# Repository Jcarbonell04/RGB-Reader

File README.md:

# RGB Reader

**Abstract**

I will be attempting to create a small colour reader device. The RGB Reader will include a colour sensor to read the rgb values and oled sceen to display. For the demo, I intend to to get paint sample strips of red, green, and, blue when I demo my reader.

**Hardware**

I have chosen the [STM32G031](https://www.digikey.ca/en/products/detail/stmicroelectronics/STM32G031K6T6/10300266?gclsrc=aw.ds&gad_source=1&gad_campaignid=17336435733&gbraid=0AAAAADrbLlg0N1Kd5EXrgzAC7LUfLDUnC&gclid=CjwKCAjwiY_GBhBEEiwAFaghvhG4pRAglKmtf1LMJkXjHH9BUgq6LzggdycpZ285lm5ClKIdZo-x5xoCx5gQAvD_BwE) as the microcontroller as there are resources given from the instructor to give me a soft start. I have not this microcontroller before, so I will have to do some research.
Supply Voltage: 1.7 V to 3.6 V

The RGB Reader will be based on a photoelectric/colour sensor. From a wide selection, I have chosen the [TCS34725 COLOR LIGHT-TO-DIGITAL CONVERTER](https://cdn-shop.adafruit.com/datasheets/TCS34725.pdf). I intend to use it because it contains an I<sup>2</sup>C interface, but seeing it is a popular choice with the STM32 gives me more confidence in choosing it. I do not have a library at the moment, but adafruit has library support for the arduino so I can start from there.
Supply Voltage: 2.7 V to 3.6 V

The display to the user will be a standard [SSD1306 128x64 I2C OLED display](https://www.amazon.ca/IZOKEE-Display-SSD1306-Raspberry-Yellow-Blue-IIC/dp/B076PNP2VD/ref=sr_1_4?crid=YXRJPVLMW9EL&dib=eyJ2IjoiMSJ9.OiybhU4XaNG6ShwJSbKTDJvkYVE5uWbfoGIpsV5YLpBxJZDEaTAqdDtPy0tWRoJ52zOXuq_cxh_j7TJz6rQsvuurKs-8koC1GKyBl8pSYDMVw_H9vG4T5x3UwTL4c-0G3metweLWxYmtzTT2dfp_ICcF3H6XFZ6SrumeL0oEe4TA_5mWreyuYLR2lQpLqmIKqqdcu85n4UoGaor2EPOOpFk7buL7VHgKdXirYBa8lvgnERpXD73-6vSLab_szAls09LM63wOs_da7XiV6JCm6I8Yke89vqq1vI80AT_NoQA.8lL2_YlI-GB7R8w4wl2GavAd1IDedNfI48C0q6DILyc&dib_tag=se&keywords=ssd1306&qid=1757697723&s=electronics&sprefix=ssd1306%2Celectronics%2C93&sr=1-4). I will be leveraging the libraries resourced from the class BrightSpace.

Supply Voltage: The logic and I2C interface for the SSD1306 typically operate at 3.3V or 5V. 
Panel Voltage: The OLED panel itself requires a higher voltage, usually between 7V and 15V, to light  the pixels. (STILL IT ONLY NEEDS 5V)
Onboard Circuitry: Many SSD1306 boards include an integrated charge pump or boost regulator, which takes the input voltage and generates the higher voltage needed by the panel. 

This device doesn't really need to be portable, so I can power it using a micro usb.

**Research**

Things I don't know, that I will need to do research on:
- Using [SEGGER](https://www.segger.com/downloads/embedded-studio/), I haven't done it before. I will need to refer to some tutorials to get started.
- I have briefly looked at the TCS34725, all I saw was that it was poplular, uses I<sup>2</sup>C too. There are many resources on the internet for this specific sensor which gives me more confidence
- I will need to research how to implement a micro usb plug in for my design. I will need it to program and power my microcontroller
  
**Proof of Concept**

For my proof-of-life build, I will be using a development board that fits into a breadboard. I have chosen the presxisting [NUCLEO-G031K8](https://www.digikey.ca/en/products/detail/stmicroelectronics/NUCLEO-G031K8/10321671?s=N4IgTCBcDaIHIFcDGAbApgewAQHEAMAzAIwgC6AvkA) for my build. This will be powered with a USB connector from a host pc. I probably have a cable for this at home

**Stretch Goals**

If I enough time is permitted, I would like to try adding a RBG light to replicate the colour values from the sensor. The only issues that I have is relying on true colour detection. Amibient light could affect the true colour. I can decide this later.

**Final Build**

For my Final build, I would like to design and 3D Print a case for my RGB Reader. My main concern is that I do not have too much experience 3D printing, so I will have to do some research. For designing, I will the software [TinkerCAD](https://www.tinkercad.com/). I have used TinkerCAD before, but never got the chance or oppurtunity to physically print out anything. I need to design my case to enclose the sensor in a way where amibient light does not affect the values read. For example, the cool lighting could affect the output by increasing the B value.

The PCB will include the main components listed earlier. The only difference between the PCB build and the proof of life build the use of the Nucleo development board in the breadboard version. I will have to design my PCB and case to allocate space for the programmer, and other parts needed for it to work. More research needs to be done before I get to the case desgining.

**Unpopulated PCB Photos**

**Schedule**

Week 1-2:
- [x] Finalize Design (Project Proposal)
- [x] Procure proof-of-life components (MCU carrier, battery options)

Week 3-4:
- [x] Assemble proof-of-life components
- [x] Master toolchain, begin software development

Week 5-6:
- [x] Finalize design, complete initial software design

Week 7-9:
- [x] Complete PCB design, software essentially complete
- [x] Complete dimensions for case know, begin 3D case design around PCB dimensions

Week 10:
- [x] Send out PCB design for manufacture

When PCBs arrive:
- [x] assemble, program, and test with current software.
- [x] complete added features, assemble into case

Finished Dec 12 2025!

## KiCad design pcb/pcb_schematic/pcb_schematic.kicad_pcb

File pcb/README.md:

# PCB Design

All design files for your PCB version of your project go here.

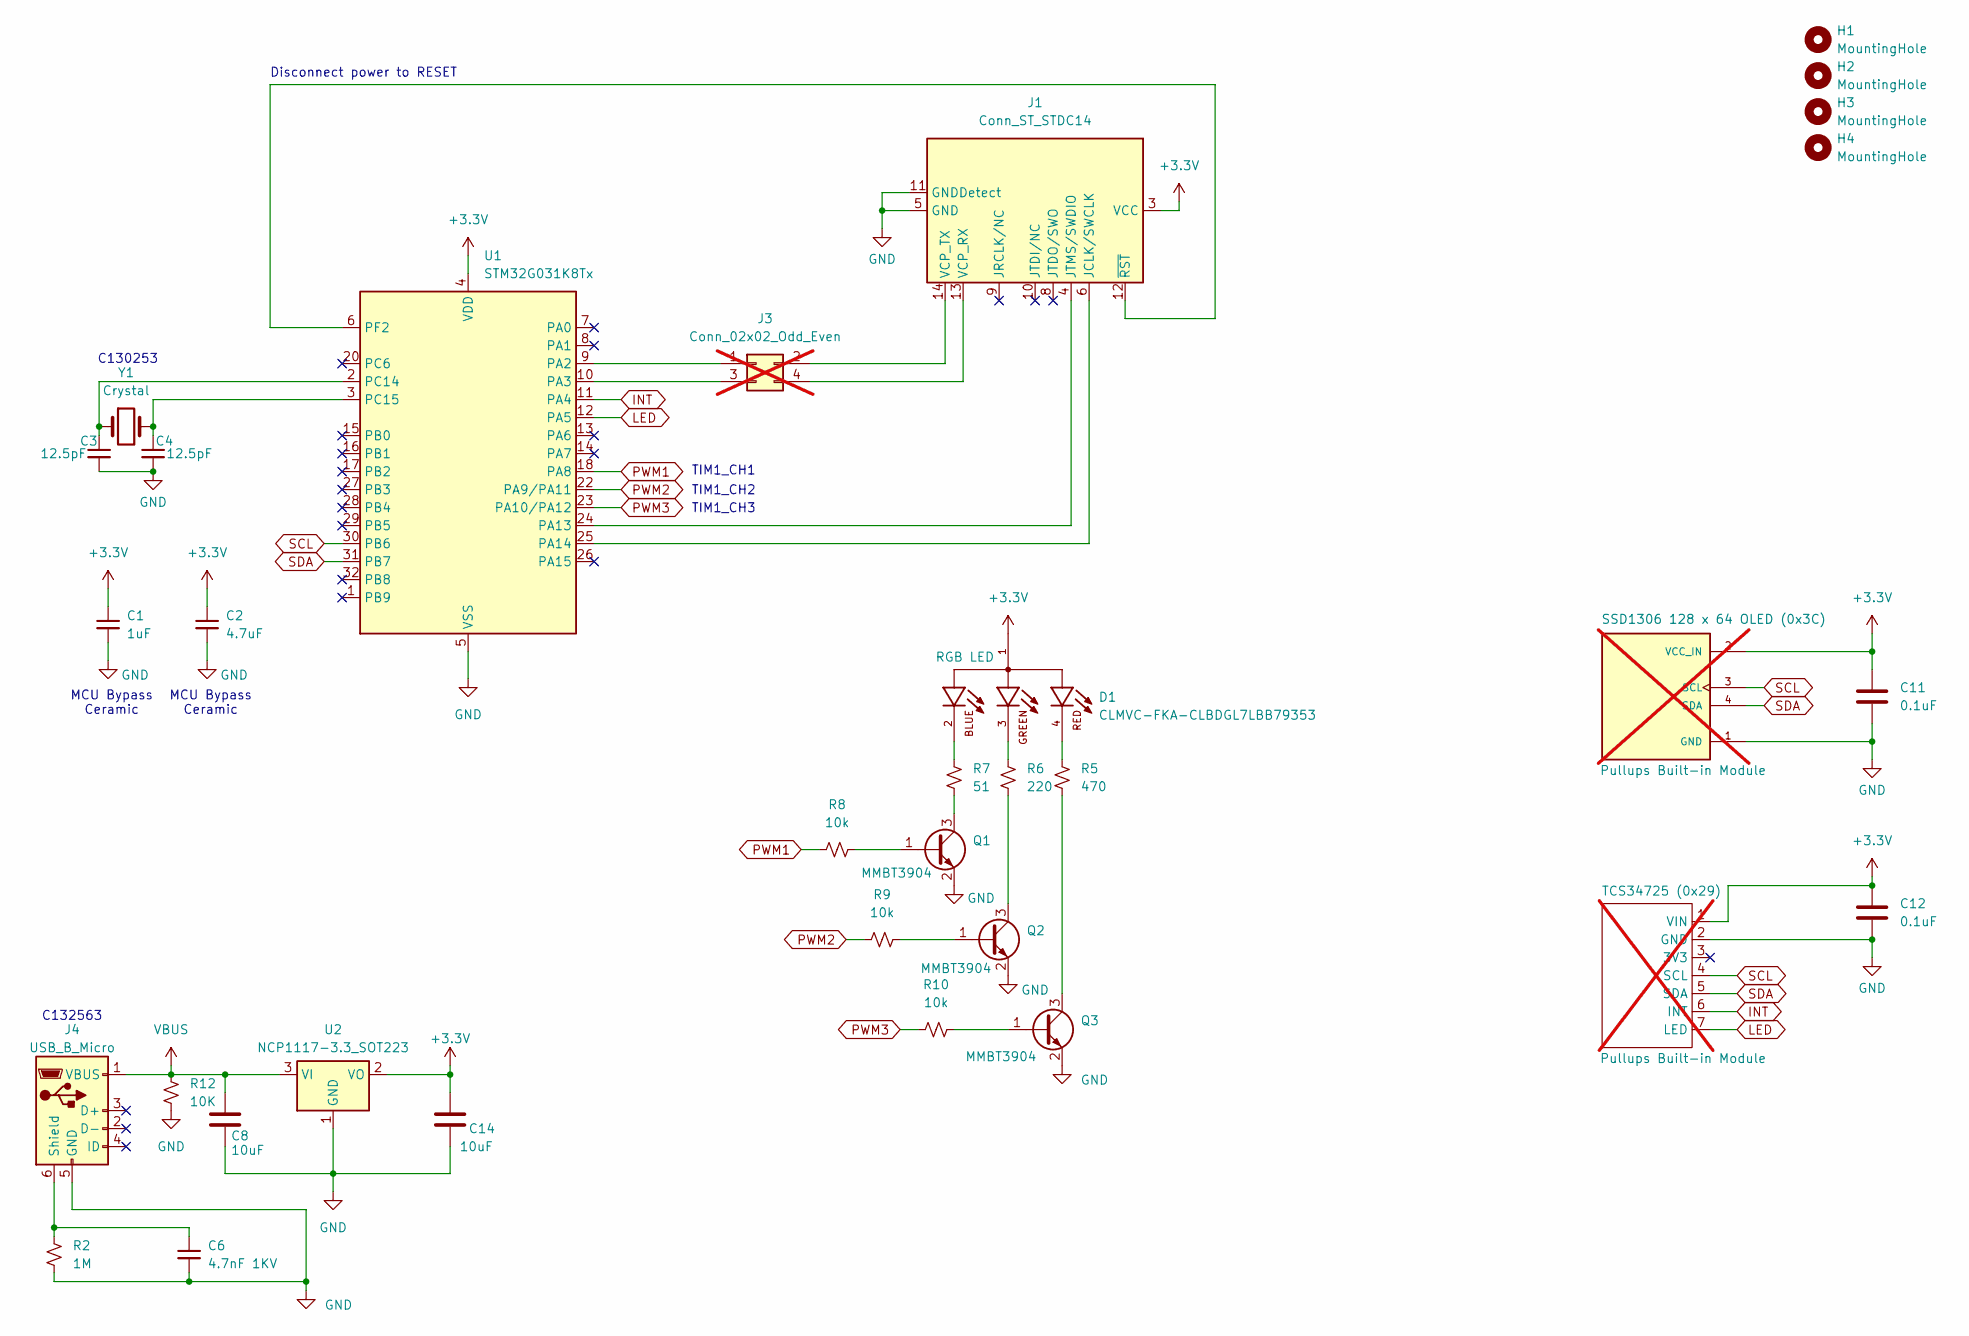
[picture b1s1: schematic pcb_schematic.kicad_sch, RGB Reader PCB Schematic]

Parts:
C1: 1uF; C_0805_2012Metric
C2: 4.7uF; C_0805_2012Metric
C3, C4: 12.5pF; C_0805_2012Metric
C6: 4.7nF 1KV; C_0805_2012Metric
C8, C14: 10uF; C_0805_2012Metric
C11, C12: 0.1uF; C_0805_2012Metric
D1: CLMVC-FKA-CLBDGL7LBB79353; LED_CLMVC-FKA-CLBDGL7LBB79353; PARTREV 14
H1, H2, H3, H4: MountingHole; MountingHole_3.2mm_M3
J1: Conn_ST_STDC14; PinHeader_2x07_P1.27mm_Vertical_SMD
J3: Conn_02x02_Odd_Even; PinHeader_2x02_P2.54mm_Vertical; not fitted
J4: USB_B_Micro; USB_Micro-B_Amphenol_10118194_Horizontal
Q1, Q2, Q3: MMBT3904; SOT-23
R2: 1M; R_0805_2012Metric
R5: 470; R_0805_2012Metric
R6: 220; R_0805_2012Metric
R7: 51; R_0805_2012Metric
R8, R9, R10: 10k; R_0805_2012Metric
R12: 10K; R_0805_2012Metric
U1: STM32G031K8Tx; LQFP-32_7x7mm_P0.8mm
U2: NCP1117-3.3_SOT223; SOT-223-3_TabPin2
U4: SSD1306 128 x 64 OLED (0x3C); 128x64OLED; PARTREV 2018-09-10; not fitted
U5: TCS34725 (0x29); TCS34725; not fitted
Y1: Crystal; Crystal_SMD_3215-2Pin_3.2x1.5mm

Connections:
+3.3V: C1.1, C2.1, C11.1, C12.1, C14.2, D1.1, J1.3 (VCC), U1.4 (VDD), U2.2 (VO), U4.2 (VCC_IN), U5.1 (VIN)
GND: C1.2, C2.2, C3.2, C4.2, C6.2, C8.1, C11.2, C12.2, C14.1, J1.5 (GND), J1.7 (GND), J1.11 (GNDDetect), J4.5 (GND), Q1.2 (E), Q2.2 (E), Q3.2 (E), R2.2, R12.1, U1.5 (VSS), U2.1 (GND), U4.1 (GND), U5.2 (GND)
INT: U1.11 (PA4), U5.6 (INT)
LED: U1.12 (PA5), U5.7 (LED)
unnamed: D1.2, R7.1
unnamed: D1.3, R6.1
unnamed: D1.4, R5.1
unnamed: J1.6 (JCLK/SWCLK), U1.25 (PA14)
unnamed: J1.4 (JTMS/SWDIO), U1.24 (PA13)
unnamed: J1.13 (VCP_RX), J3.4
unnamed: J1.14 (VCP_TX), J3.2
unnamed: J1.12 (~RST), U1.6 (PF2)
unnamed: J3.1, U1.9 (PA2)
unnamed: J3.3, U1.10 (PA3)
unnamed: C6.1, J4.6 (Shield), R2.1
unnamed: Q1.1 (B), R8.2
unnamed: Q1.3 (C), R7.2
unnamed: Q2.1 (B), R9.2
unnamed: Q2.3 (C), R6.2
unnamed: Q3.1 (B), R10.2
unnamed: Q3.3 (C), R5.2
unnamed: C3.1, U1.2 (PC14), Y1.1
unnamed: C4.1, U1.3 (PC15), Y1.2
PWM1: R8.1, U1.18 (PA8)
PWM2: R9.1, U1.22 (PA9/PA11)
PWM3: R10.1, U1.23 (PA10/PA12)
SCL: U1.30 (PB6), U4.3 (SCL), U5.4 (SCL)
SDA: U1.31 (PB7), U4.4 (SDA), U5.5 (SDA)
VBUS: C8.2, J4.1 (VBUS), R12.2, U2.3 (VI)

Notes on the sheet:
TIM1_CH3
TIM1_CH2
TIM1_CH1
C132563
MCU Bypass Ceramic
Disconnect power to RESET
C130253

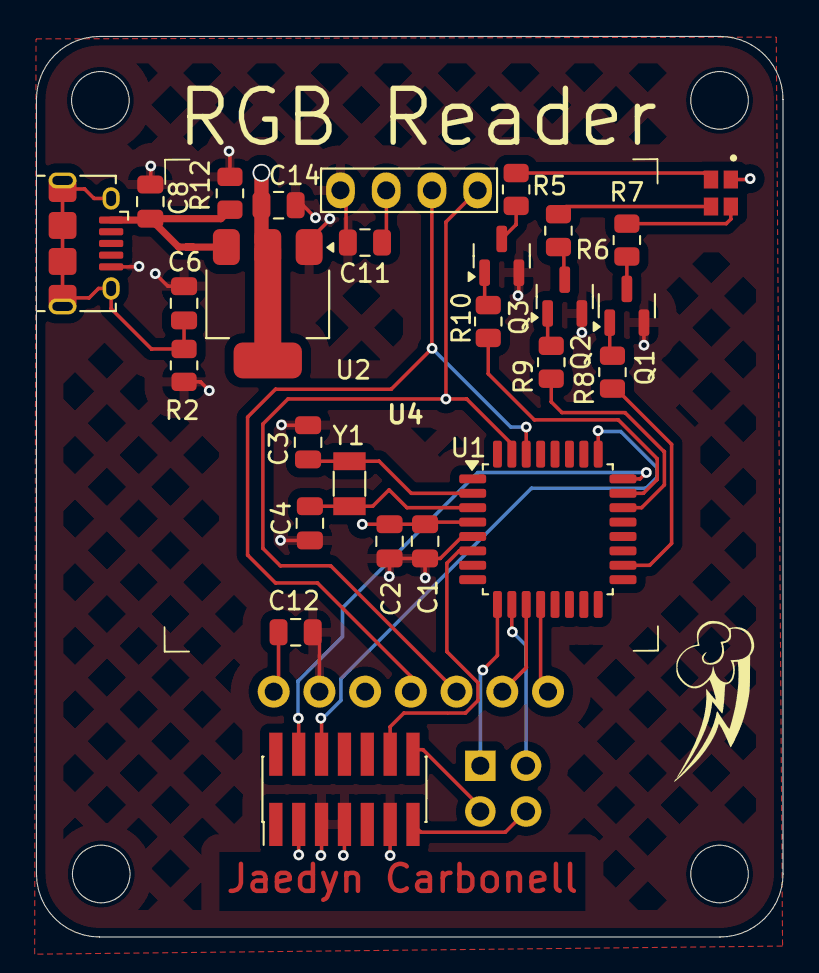
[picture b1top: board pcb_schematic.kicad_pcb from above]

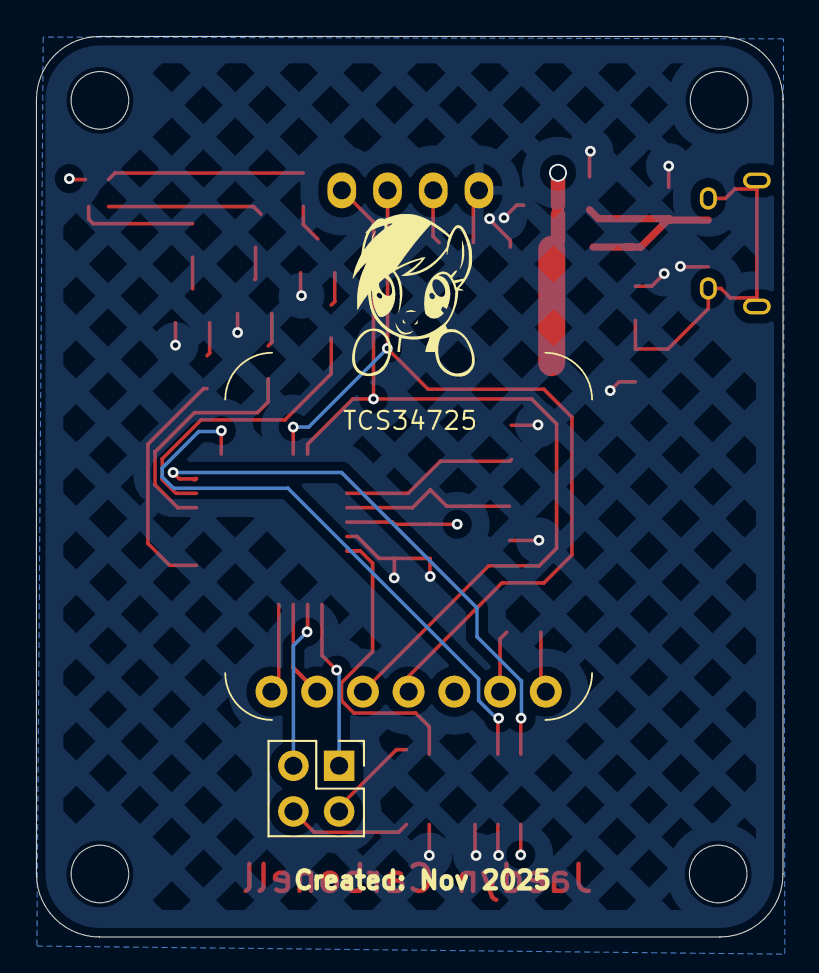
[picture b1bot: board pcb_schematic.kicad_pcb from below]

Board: 4 copper layers, 41.5 x 50.0 mm, 33 parts (2 on the bottom side), 29 nets.

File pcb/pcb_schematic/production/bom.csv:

Designator,Footprint,Quantity,Value,LCSC Part #
C1,0805,1,1uF,
"C11, C12",0805,2,0.1uF,
"C14, C8",0805,2,10uF,
C2,0805,1,4.7uF,
"C3, C4",0805,2,12.5pF,
C6,0805,1,4.7nF 1KV,
D1,LED_CLMVC-FKA-CLBDGL7LBB79353,1,CLMVC-FKA-CLBDGL7LBB79353,
J1,PinHeader_2x07_P1.27mm_Vertical_SMD,1,Conn_ST_STDC14,
J4,USB_Micro-B_Amphenol_10118194_Horizontal,1,USB_B_Micro,
"Q1, Q2, Q3",SOT-23,3,MMBT3904,
"R10, R12, R8, R9",0805,4,10k,
R2,0805,1,1M,
R5,0805,1,470,
R6,0805,1,220,
R7,0805,1,51,
U1,LQFP-32_7x7mm_P0.8mm,1,STM32G031K8Tx,
U2,SOT-223-3_TabPin2,1,NCP1117-3.3_SOT223,
Y1,Crystal_SMD_3215-2Pin_3.2x1.5mm,1,Crystal,

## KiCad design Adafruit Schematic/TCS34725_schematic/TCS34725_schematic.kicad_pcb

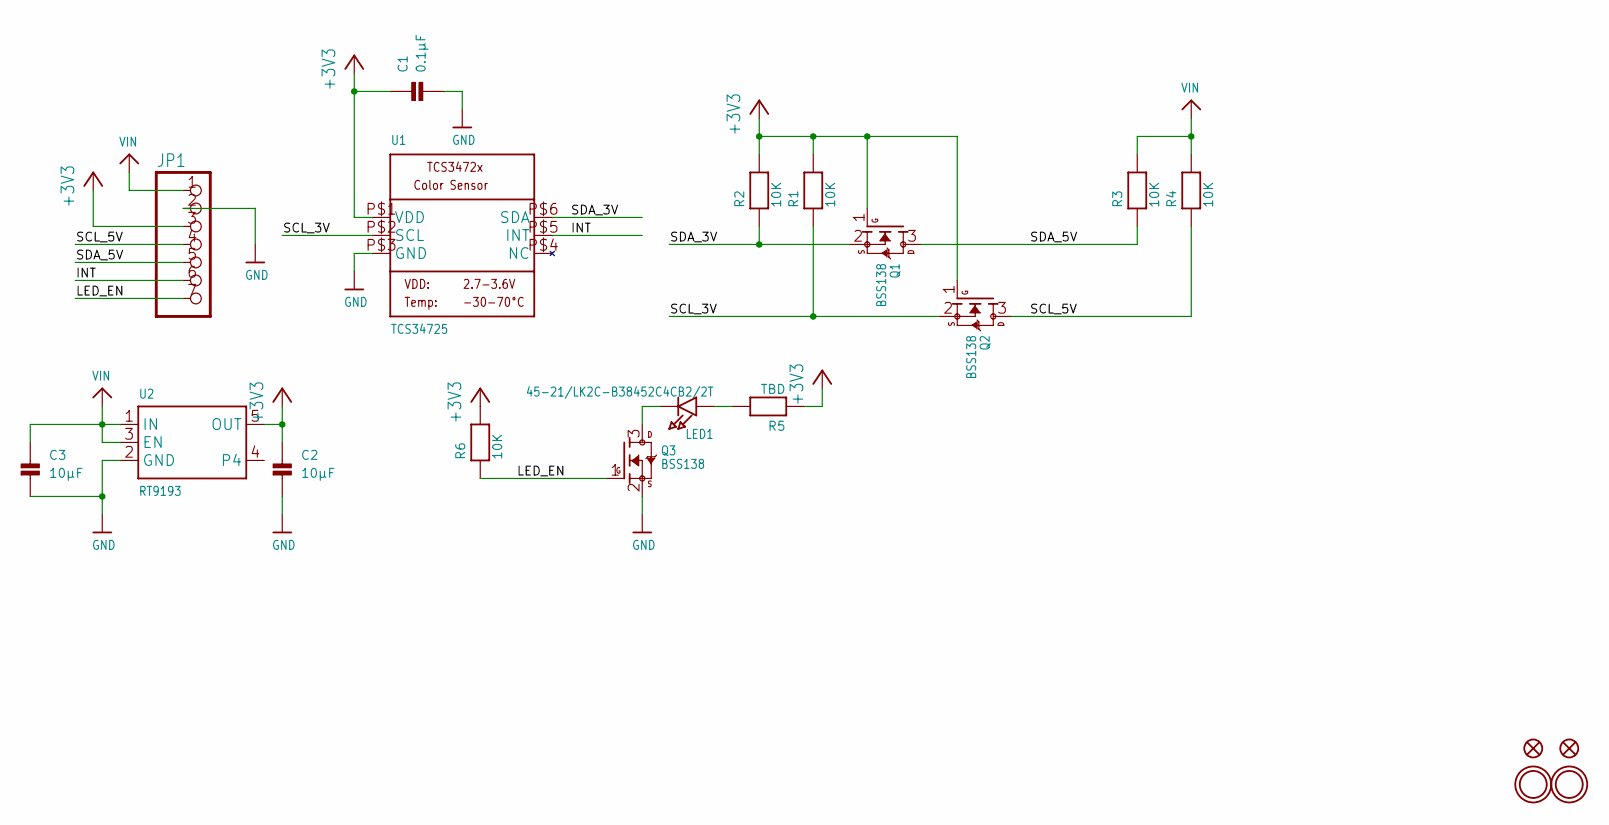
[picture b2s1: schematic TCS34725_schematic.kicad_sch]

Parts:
C1: 0.1µF; _0805
C2, C3: 10µF; _0805
FID1, FID2: FIDUCIAL""; FIDUCIAL_1MM
JP1: HEADER-1X770MIL; 1X07_ROUND_70
LED1: 45-21/LK2C-B38452C4CB2/2T; EVERLIGHT_45-21
Q1, Q2, Q3: BSS138; SOT23-WIDE
R1, R2, R3, R4, R6: 10K; _0805
R5: TBD; _0805
U1: TCS34725; TCS3472_FN6
U2: RT9193; SOT23-5
U$8, U$14: MOUNTINGHOLE2.5; MOUNTINGHOLE_2.5_PLATED

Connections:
+3V3: C1.1, C2.1, JP1.3, Q1.1 (G), Q2.1 (G), R1.2, R2.2, R5.1, R6.2, U1.P$1 (VDD), U2.5 (OUT)
GND: C1.2, C2.2, C3.2, JP1.2, Q3.2 (S), U1.P$3 (GND), U2.2 (GND)
INT: JP1.6, U1.P$5 (INT)
LED_EN: JP1.7, Q3.1 (G), R6.1
unnamed: LED1.K (C), Q3.3 (D)
unnamed: LED1.A, R5.2
SCL_3V: Q2.2 (S), R1.1, U1.P$2 (SCL)
SCL_5V: JP1.4, Q2.3 (D), R4.1
SDA_3V: Q1.2 (S), R2.1, U1.P$6 (SDA)
SDA_5V: JP1.5, Q1.3 (D), R3.1
VIN: C3.1, JP1.1, R3.2, R4.2, U2.1 (IN), U2.3 (EN)

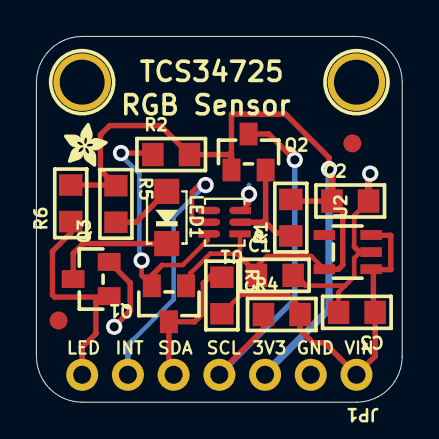
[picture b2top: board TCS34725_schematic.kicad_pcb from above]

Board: 2 copper layers, 20.3 x 20.3 mm, 22 parts (1 on the bottom side), 11 nets.

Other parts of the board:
U$2: ADAFRUIT_2.5MM
U$18: ADAFRUIT_5MM

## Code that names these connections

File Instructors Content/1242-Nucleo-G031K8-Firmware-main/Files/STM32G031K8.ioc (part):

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Mcu.Name=STM32G031K(4-6-8)Tx
Mcu.Package=LQFP32
Mcu.UserName=STM32G031K8Tx
PA10.Mode=I2C
PA10.Signal=I2C1_SDA
PA13.GPIOParameters=GPIO_Label
PA13.GPIO_Label=T_JTMS
PA13.Mode=Serial_Wire
PA13.Signal=SYS_SWDIO
PA14-BOOT0.GPIOParameters=GPIO_Label
PA14-BOOT0.GPIO_Label=T_JTCK
PA14-BOOT0.Mode=Serial_Wire
PA14-BOOT0.Signal=SYS_SWCLK
PA2.GPIOParameters=GPIO_PuPd,GPIO_Label
PA2.GPIO_Label=T_VCP_TX
PA2.GPIO_PuPd=GPIO_PULLUP
PA2.Mode=Asynchronous
PA2.Signal=USART2_TX
PA3.GPIOParameters=GPIO_PuPd,GPIO_Label
PA3.GPIO_Label=T_VCP_RX
PA3.GPIO_PuPd=GPIO_PULLUP
PA3.Mode=Asynchronous
PA3.Signal=USART2_RX
PA8.Mode=Clock-out
PA8.Signal=RCC_MCO
PA9.Mode=I2C
PA9.Signal=I2C1_SCL
PC14-OSC32_IN\ (PC14).Mode=LSE-External-Oscillator
PC14-OSC32_IN\ (PC14).Signal=RCC_OSC32_IN
PC15-OSC32_OUT\ (PC15).Mode=LSE-External-Oscillator
PC15-OSC32_OUT\ (PC15).Signal=RCC_OSC32_OUT
PC6.GPIOParameters=GPIO_Label
PC6.GPIO_Label=LD3 [Green]
PC6.Signal=GPIO_Output
PF2\ -\ NRST.GPIOParameters=GPIO_Label
PF2\ -\ NRST.GPIO_Label=T_NRST
PF2\ -\ NRST.Signal=GPXTI2
RCC.HSE_VALUE=8000000
RCC.SYSCLKFreq_VALUE=25000000
RCC.SYSCLKSource=RCC_SYSCLKSOURCE_PLLCLK
board=NUCLEO-G031K8
boardIOC=true

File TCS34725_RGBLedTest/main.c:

// Author: Jaedyn Carbonell
// Desc: Reading RGB values on SSD1306 (OLED) from TCS34725 (colour sensor) + LED
// Core clock: 64MHz
// Notes:
// Requires I2C1 on PB6/PB7 (SCL/SDA) to communicate with OLED
// PA8  - TIM1 CH1 R
// PA9  - TIM1 CH2 G
// PA10 - TIM1 CH3 B


#include "stm32g031xx.h"
#include <stdio.h>
#include "gpio.h"
#include "pll.h"
#include "usart.h"
#include "i2c.h"
#include "SSD1306.h"
#include "TCS34725.h"

// function prototypes
void _OneTimeInits(void);
uint16_t ScaleToPWM(uint16_t val, uint16_t clear);

TCS34725_t colourSensor;

const uint16_t PWM_MAX = 63999;

uint16_t ScaleToPWM(uint16_t val, uint16_t clear)
{
    if (clear == 0) return 0;

    float norm = (float)val / (float)clear; 
    float pwm  = norm * PWM_MAX;

    if (pwm < 0)       pwm = 0;
    if (pwm > PWM_MAX) pwm = PWM_MAX;

    return (uint16_t)pwm;
}

// -----------------------------------------------------
int main(void)
{
    _PLL_To_64();
    _OneTimeInits();

    _USART2_TxStringXY(1, 6, "Initializing TCS34725...");

    // Initialize sensor
    if (!_TCS34725_Init(&colourSensor))
    {
        _USART2_TxStringXY(1, 7, "TCS34725 not found!");
        _SSD1306_StringXY(0, 0, "TCS34725 not found!");
        _SSD1306_Render();
        while (1);
    }

    _USART2_TxStringXY(1, 7, "TCS34725 ready!");
    _SSD1306_Clear();
    _SSD1306_StringXY(0, 0, "TCS34725 ready!");
    _SSD1306_Render();

    uint16_t r, g, b, c;
    char buff[64];

    while (1)
    {
        // Read raw sensor data
        _TCS34725_GetRawData(&colourSensor, &r, &g, &b, &c);

        // PWM UPDATE FOR RGB LED 
        TIM1->CCR1 = ScaleToPWM(r, c);   // Red
        TIM1->CCR2 = ScaleToPWM(g, c);   // Green
        TIM1->CCR3 = ScaleToPWM(b, c);   // Blue

        // OLED Display
        _SSD1306_Clear();
        sprintf(buff, "R:%5u", r);
        _SSD1306_StringXY(0, 0, buff);
        sprintf(buff, "G:%5u", g);
        _SSD1306_StringXY(0, 1, buff);
        sprintf(buff, "B:%5u", b);
        _SSD1306_StringXY(0, 2, buff);
        sprintf(buff, "C:%5u", c);
        _SSD1306_StringXY(0, 3, buff);
        _SSD1306_Render();

        // Serial Output
        sprintf(buff, "R:%u G:%u B:%u C:%u\r\n", r, g, b, c);
        _USART2_TxString(buff);

        for (volatile int i = 0; i < 500000; ++i); // ~500ms delay
    }
}

// -----------------------------------------------------
void _OneTimeInits(void)
{
    RCC->APBENR2 |= RCC_APBENR2_SYSCFGEN;
    SYSCFG->CFGR1 |= SYSCFG_CFGR1_PA11_RMP;
    SYSCFG->CFGR1 |= SYSCFG_CFGR1_PA12_RMP;

    // GPIOA Clock
    RCC->IOPENR |= RCC_IOPENR_GPIOAEN;

    // USART
    _USART2_Init(64E6, 38400);
    _USART2_ClearScreen();
    _USART2_TxStringXY(1, 1, "USART started...");

    // I2C1
    _USART2_TxStringXY(1, 3, "Starting I2C1 bus...");
    _I2C1_Init_PB67(100);
    _USART2_TxStringXY(1, 4, "I2C1 bus ready...");

    // OLED
    _SSD1306_DispInit(_SSD1306_OR_DOWN);
    _SSD1306_DisplayOn();
    _SSD1306_Clear();
    _SSD1306_StringXY(0, 0, "OLED Ready");
    _SSD1306_Render();

    //                 RGB LED PWM (TIM1 CH1/CH2/CH3)

    RCC->APBENR2 |= RCC_APBENR2_TIM1EN; // Enable TIM1

    // PA8 (CH1), PA9 (CH2), PA10 (CH3)
    GPIOA->MODER &= ~(GPIO_MODER_MODE8_Msk | GPIO_MODER_MODE9_Msk | GPIO_MODER_MODE10_Msk);
    GPIOA->MODER |=  (0x2 << GPIO_MODER_MODE8_Pos) |
                     (0x2 << GPIO_MODER_MODE9_Pos) |
                     (0x2 << GPIO_MODER_MODE10_Pos);

    GPIOA->AFR[1] &= ~(0xF << 0 | 0xF << 4 | 0xF << 8);
    GPIOA->AFR[1] |=  (1 << 0) | (1 << 4) | (1 << 8);  // AF1 TIM1

    // PWM Mode 1 for CH1, CH2, CH3
    TIM1->CCMR1 = (6 << 4) | TIM_CCMR1_OC1PE           // CH1
                | (6 << 12) | TIM_CCMR1_OC2PE;         // CH2

    TIM1->CCMR2 = (6 << 4) | TIM_CCMR2_OC3PE;          // CH3

    TIM1->ARR  = PWM_MAX;
    TIM1->CCR1 = 0;
    TIM1->CCR2 = 0;
    TIM1->CCR3 = 0;

    // Enable outputs
    TIM1->CCER |= TIM_CCER_CC1E | TIM_CCER_CC2E | TIM_CCER_CC3E;

    // Main output enable, TIM1 is advanced timer
    TIM1->BDTR |= TIM_BDTR_MOE;

    TIM1->CR1 |= TIM_CR1_ARPE | TIM_CR1_CEN;
}

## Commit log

2025-09-24 Added simons lib
2025-09-24 Added Instructors Content
2025-09-26 Oled working
2025-09-26 Proof of Life?
2025-10-02 changed
2025-10-03 organize
2025-10-03 bruh
2025-10-07 working?
2025-10-08 soldered lol
2025-10-10 recieved POL checkoff
2025-10-10 added to lib
2025-10-10 lib?
2025-10-13 omg sensor working?
2025-10-13 working!
2025-10-15 help
2025-10-17 xganges
2025-10-22 finished breadboard schematic
2025-10-22 reorganized
2025-10-22 i lowkey dont know what im doing
2025-10-22 oct 22
2025-10-29 bluh
2025-10-29 v4 now?
2025-10-31 Create fp-lib-table
2025-10-31 puth
2025-10-31 almost checkoff
2025-11-04 Changed after recieving feedback
2025-11-04 PWM on Timer 1 Pins
2025-11-05 the schmatic keeps chaning i wanna cry
2025-11-05 Components are laid out
2025-11-06 before i change many thing
2025-11-06 moved rbg led
2025-11-06 Created pcb desgin, need to rid of all warning
2025-11-07 fixerd some warnings with the silkscreen
2025-11-07 Fixed according to feedback
    Schematic -> looks like the current limiting resistors for the read and blue LEDs are reversed.
    Bypass caps for the MCU are drawn really weird!
    Looks like you moved the XTAL and now you have two redundant wires.
    PCB -> Identification is in the copper layer, not the silk layer.
    C12 does not need vias, the through-hole header serves as vias.
    You've got a split on the SDA line of the MCU - try to route from a via, or another pad if you can.
2025-11-08 via error
2025-11-08 via warning
2025-11-08 added image lol
2025-11-08 Finalized?
2025-11-09 ready to order :D
2025-11-20 new project
2025-11-21 change display
2025-12-05 Revise project proposal title and abstract
    Updated the project proposal title and improved formatting.
2025-12-05 checked off!
2025-12-05 checkoff
2025-12-11 formatting
2025-12-21 Revise README for RGB Reader project
    Updated project details for RGB Reader, including hardware specifications, research areas, proof of concept, stretch goals, final build plans, and a schedule for development.
2025-12-28 Update README with completed tasks
2025-12-28 Added Datasheets
2025-12-28 Commented
2025-12-28 Removed Unused code
2026-02-02 Update README with completed tasks for Week 10
2026-02-04 Add unpopulated PCB photos to README
    Added images of the unpopulated PCB to the README.
2026-02-04 Modify PCB photo entries in README
    Updated image tags for unpopulated PCB photos in README.
